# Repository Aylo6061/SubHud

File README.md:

# SubHud
A heads up display for scuba diving

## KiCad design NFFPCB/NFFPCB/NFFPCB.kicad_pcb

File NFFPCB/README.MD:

# Non-Form-Factor PCB

non form factor prototype board to explore mounting the bare screen + battery charger.

# BUGS

-pin 9 #RES of oled needs to be pulled up - bodge wired to oled EN
-Q2 neds DS swapped (oops). Fixed on pcb

# TODO

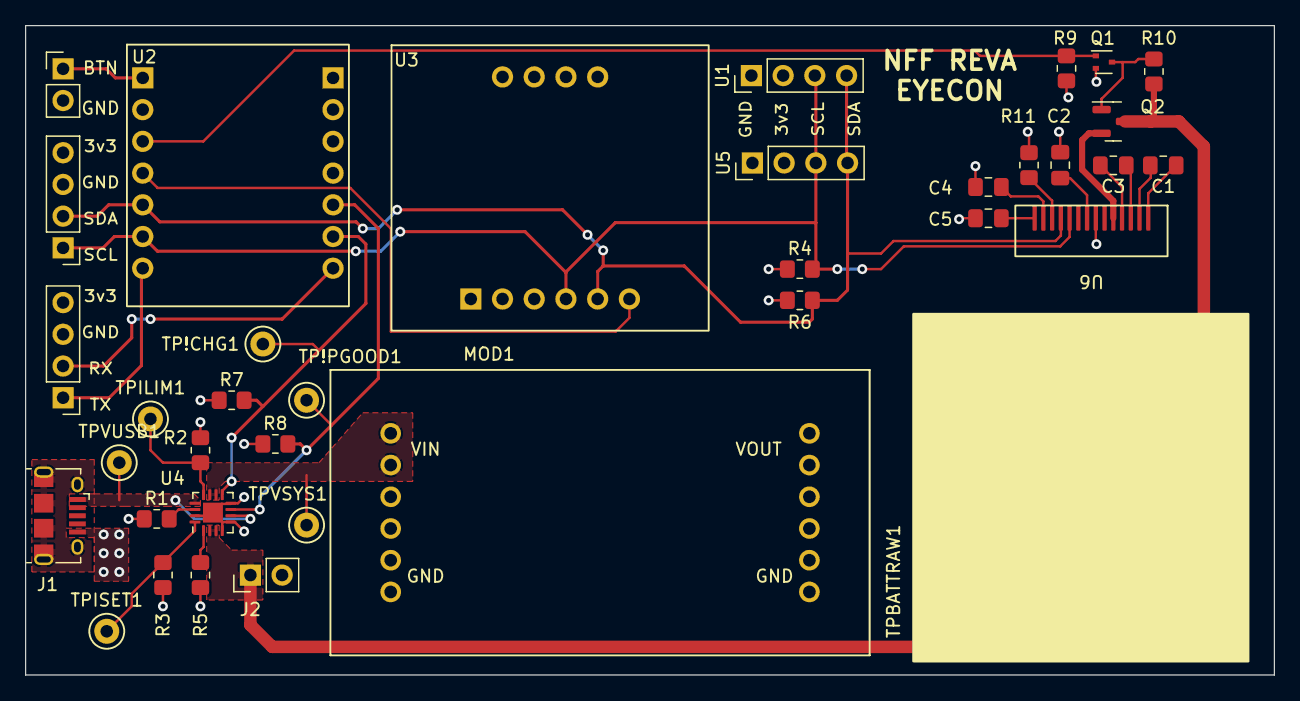
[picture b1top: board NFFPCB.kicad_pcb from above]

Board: 4 copper layers, 100.0 x 52.0 mm, 37 parts (0 on the bottom side), 28 nets.

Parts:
C1, C2, C3, C4, C5: C; C_0805_2012Metric_Pad1.18x1.45mm_HandSolder
J1: USB_B_Micro; USB_Micro-B_Amphenol_10118194_Horizontal
J2, J3: Conn_01x02_Female; PinHeader_1x02_P2.54mm_Vertical
J4, J5: Conn_01x04_Female; PinHeader_1x04_P2.54mm_Vertical
MOD1: TPS61220EVM; TPS51220EVM
Q1: Q_NMOS_GSD; SOT-523
Q2: Q_PMOS_GSD; SOT-23
R1: 46k4; R_0805_2012Metric_Pad1.20x1.40mm_HandSolder
R2: 3k0; R_0805_2012Metric_Pad1.20x1.40mm_HandSolder
R3: 7k5; R_0805_2012Metric_Pad1.20x1.40mm_HandSolder
R4, R6, R9, R10, R11: R; R_0805_2012Metric_Pad1.20x1.40mm_HandSolder
R5, R7, R8: 10k; R_0805_2012Metric_Pad1.20x1.40mm_HandSolder
TP!CHG1: TestPoint; TestPoint_Keystone_5000-5004_Miniature
TP!PGOOD1: TestPoint; TestPoint_Keystone_5000-5004_Miniature
TPBATTRAW1: TestPoint; TestPoint_Keystone_5000-5004_Miniature
TPILIM1: TestPoint; TestPoint_Keystone_5000-5004_Miniature
TPISET1: TestPoint; TestPoint_Keystone_5000-5004_Miniature
TPVSYS1: TestPoint; TestPoint_Keystone_5000-5004_Miniature
TPVUSB1: TestPoint; TestPoint_Keystone_5000-5004_Miniature
U1: MS5837 breakout; PinHeader_1x04_P2.54mm_Vertical
U2: Adafruit_QTPY_ESP32-C3; QTPY ESP32 C3
U3: Adafruit_BNO_055
U4: BQ24072RGT; VQFN-16-1EP_3x3mm_P0.5mm_EP1.6x1.6mm
U5: ER-OLED0.49-1_MODULE; PinHeader_1x04_P2.54mm_Vertical
U6: ER-OLED0.49-1; ER OLED49.0

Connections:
+3V3: J4.4, J5.4, MOD1.3 (VOUT), R4.1, R6.1, R7.1, R8.1, U1.2 (VCC), U2.12 (3v3), U3.6 (3V), U5.2 (VCC)
/!CHG: R7.2, TP!CHG1.1, U2.9 (SCK), U4.9 (~CHG)
/!PGOOD: R8.2, TP!PGOOD1.1, U2.10 (MISO), U4.7 (~PGOOD)
/+VUSB: J1.1 (VBUS), TPVUSB1.1, U4.6 (EN1), U4.13 (IN)
/BNO_RST: U2.4 (A3), U3.10 (RST)
/BUTTON: J3.1, U2.1 (A0)
/C1N: C3.2, U6.4 (C1N)
/C1P: C3.1, U6.3 (C1P)
/C2N: C1.2, U6.2 (C2N)
/C2P: C1.1, U6.1 (C2P)
/OLED_EN: Q1.1 (G), R9.2, U2.3 (A2)
/RX_TO_MICRO: J4.2, U2.8 (RX)
/SCL: J5.1, R4.2, U1.3 (SCL), U2.6 (SCL), U3.8 (SCL), U5.3 (SCL), U6.10 (SCL)
/SDA: J5.2, R6.2, U1.4 (SDA), U2.5 (SDA), U3.9 (SDA), U5.4 (SDA), U6.11 (SDA)
/TX_FROM_MICRO: J4.1, U2.7 (TX)
/VBATT_RAW: J2.1, Q2.3 (D), R10.1, TPBATTRAW1.1, U4.2 (BAT), U4.3 (BAT)
/VBAT_OLED: Q2.2 (S), U6.5 (VBAT)
/VSYS: MOD1.1 (VIN), TPVSYS1.1, U4.10 (OUT), U4.11 (OUT)
GND: C2.2, C4.2, C5.2, J1.5 (GND), J2.2, J3.2, J4.3, J5.3, MOD1.2 (GND), MOD1.4 (GND), Q1.2 (S), R1.1, R2.1, R3.1, R5.1, R9.1, R11.2, U1.1 (GND), U2.13 (GND), U3.7 (GND), U4.4 (~CE), U4.5 (EN2), U4.8 (VSS), U4.15 (TD), U4.17 (VSS), U5.1 (GND), U6.7 (VSS)
unnamed: C2.1, U6.8 (VDD)
unnamed: C4.1, U6.13 (VCOMH)
unnamed: C5.1, U6.14 (VCC)
unnamed: Q1.3 (D), Q2.1 (G), R10.2
unnamed: R1.2, U4.14 (TMR)
unnamed: R2.2, TPILIM1.1, U4.12 (ILIM)
unnamed: R3.2, TPISET1.1, U4.16 (ISET)
unnamed: R5.2, U4.1 (TS)
unnamed: R11.1, U6.12 (IREF)

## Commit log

2022-12-30 committing NFF PCB
2022-12-30 initial fw commit
2023-04-07 testing some power down changes
